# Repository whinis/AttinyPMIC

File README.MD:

### Project

I was working on a project where I wanted a soft On/Off button such that whenever you pressed a button the power turned on but whenever you held the button the power turned off, low power as it was a battery powered application, and could work even if the main microprocessor locked up or had another error. I was shocked to learn there was few parts for this application and the ones that did exists were expensive relative to everything else. I started looking into different ways of doing this and they all either involved a ton of board space and drew a fairly significant amount(1ma+) of power or cost upwards more than $1 per IC which in hobby price is outrageous.  So I tried another route.

This implementation takes an Attiny4,5,6 or 10 and implements an interrupt on one pin that should be connected to a standard push button. One pin is used as a general interrupt to inform the button has been pressed. Another pin is used as an output to either a transistor, ideal diode, or regulator, this pin is pulled high as an input once the button is pressed. Once the button is held down for ~ 5 seconds the output pin is pulled low as an output before becoming an input again. The attiny is asleep outside of these events. The reset pin is left unchanged so that you can easily reprogram

### Features
- Low cost ($0.27 per attiny)
- Low Power (<0.1µa)
- Allows Microprocessor to control output as well 
Since the output in is just an input with a pullup its easy to overpower with a true output or in testing. The software will monitor or external force forcing the pin low and disable its output as well.
- Small form factor (Sot23-6 or UDFN-8)
- Configurable
	With this being a micro rather than fixed silicon you can change which pins do which if your designs change without issue

### In this Repository
In the code directory is the main.c that contains the code. It was made in [https://github.com/wholder/ATTiny10IDE](https://github.com/wholder/ATTiny10IDE "https://github.com/wholder/ATTiny10IDE") which is a wonderful simple IDE for Attiny10 family of microprocessors. You can program to the Attiny using a standard arduino.

In the Hardware directory is some breakout board files in Kicad I used on my breadboards and can be used as example circuits. Both boards use a LDO on the board to control the output level of the attiny 10, if you are not using the interrupt you can likely connect directly to your battery. PMIC v2 uses a LDO that makes the entire circuit < 1µa which should be less than most batteries self-discharge rate.

Images contains images of the breakout board.

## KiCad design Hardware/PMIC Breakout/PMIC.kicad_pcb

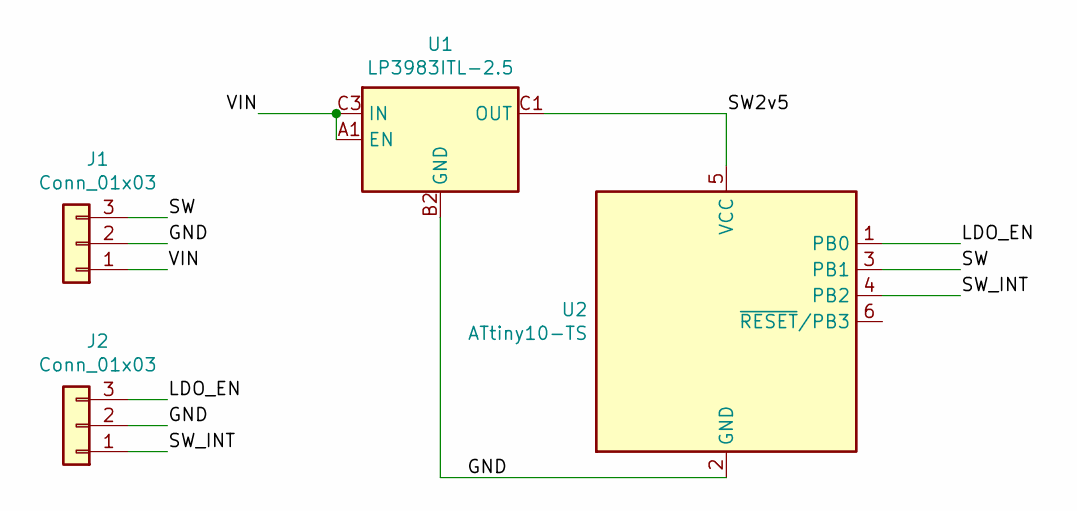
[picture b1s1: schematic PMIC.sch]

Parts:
J1, J2: Conn_01x03; PinHeader_1x03_P2.54mm_Vertical
U1: LP3983ITL-2.5; Texas_DSBGA-5_0.822x1.116mm_Layout2x1x2_P0.4mm
U2: ATtiny10-TS; SOT-23-6

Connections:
/GND: J1.2, J2.2, U1.B2 (GND), U2.2 (GND)
/LDO_EN: J2.3, U2.1 (PB0)
/SW: J1.3, U2.3 (PB1)
/SW2v5: U1.C1 (OUT), U2.5 (VCC)
/SW_INT: J2.1, U2.4 (PB2)
/VIN: J1.1, U1.A1 (EN), U1.C3 (IN)

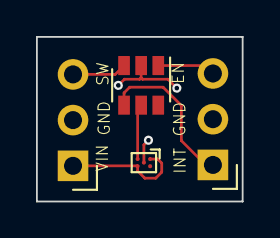
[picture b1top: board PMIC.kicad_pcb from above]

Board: 2 copper layers, 11.4 x 9.1 mm, 4 parts (0 on the bottom side), 6 nets.

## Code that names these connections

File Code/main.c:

#pragma chip attiny10
#pragma lfuse 0x62          // default value
#pragma hfuse 0xDF          // default value
#pragma efuse 0xFF          // default value


#define F_CPU 256000UL
#include <avr/io.h>
#include <avr/interrupt.h>
#include <avr/sleep.h>
#include <util/delay.h>

void goToSleep ();

uint8_t button = 0;

#define BUTTON PB1			// Pin used as button to trigger LDO_EN
#define INT_OUT PB2			// Pin used as interrupt to inform other things button was pressed
#define LDO_EN PB2			// Pin used to enable LDO
#define HOLD_TIME 300		// counter button is held for before disabling LDO_EN


int main () {
	CCP = 0xD8;			    // Unprotect CLKPSR reg
  	CLKPSR = 5;             // Set clock to 64khz
	OSCCAL=0x59;
	ADCSRA &= ~_BV(ADEN);	// Disable ADC, we never need it
	PCICR = 1;				// Enable Pin Change Interrupt
	PCMSK  |= _BV(PCINT1)   // Enables Pin Change on PCINT1
			| _BV(PCINT0);  // Enables Pin Change on PCINT0

	PUEB |=_BV(BUTTON);		//Set PB2 to have a pullup
	DDRB |=_BV(INT_OUT);		//Set PB1 to be an output
	uint16_t counter = 0;
	char debounce = 0;
  	while (true) {
		if(button == 1){
			if(debounce >0)
				debounce -= 1;		//disable denounce counter
			if(counter > HOLD_TIME){ // shuts off at roughly 6 seconds
				PUEB &= ~_BV(LDO_EN);  //Disable PB0(LDO_EN) pullup to turn off
    			PORTB &= ~_BV(LDO_EN);  //Set PB0(LDO_EN) as Low
    			DDRB |= (1 << LDO_EN);	//set PB0 as output temperorarily to force off
    			debounce = 0;
			}else{
				counter+=1; //prevent counter from overflowing
			}
		}else if(counter > 0){
			debounce +=1;
			if(debounce > 15){
				counter = 0;
				debounce = 0;
			}
		}
		if(counter == 0 && debounce == 0){ //go to sleep if the power switch has not recently been pressed
			DDRB &= ~_BV(PB0);	//set PB0 as input again
			goToSleep();		// we are setup, go to sleep
		}
		_delay_ms(10);
  	}
}

void goToSleep ()
{    
	set_sleep_mode(SLEEP_MODE_PWR_DOWN);
	sleep_enable();
	sei();					// turn on interrupts
	sleep_cpu();
	sleep_disable();
}

ISR(PCINT0_vect)
{
	cli();
	//button is pressed or not pressed.
	if((PINB &_BV(BUTTON))== 0){
		PUEB |=_BV(LDO_EN);	//Set PB0(EN) to have a pullup to fake it being an output
		PORTB |= _BV(INT_OUT);	//set Interrupt to MCU
		button = 1;
	}else{
		PORTB &= ~_BV(INT_OUT); //clear Interrupt to MCU
		button = 0;
	}

	//the MCU forced off the power
	if((PINB &_BV(LDO_EN))== 0){
		PUEB &= ~_BV(LDO_EN);  //Disable PB0(EN) pullup to turn off
	}
}

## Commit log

2020-04-19 Initial Commit of AttinyPMIC Repo
